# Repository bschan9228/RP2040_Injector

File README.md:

The RP2040 Injector is a 4-layer PCB. It is essentially used as a keystroke injector. I sourced components, made the schematics and designed the PCB, and hand soldered the components onto a two-sided PCB. It utilizes an RP2040, voltage regulator, a USB Type-A connector.

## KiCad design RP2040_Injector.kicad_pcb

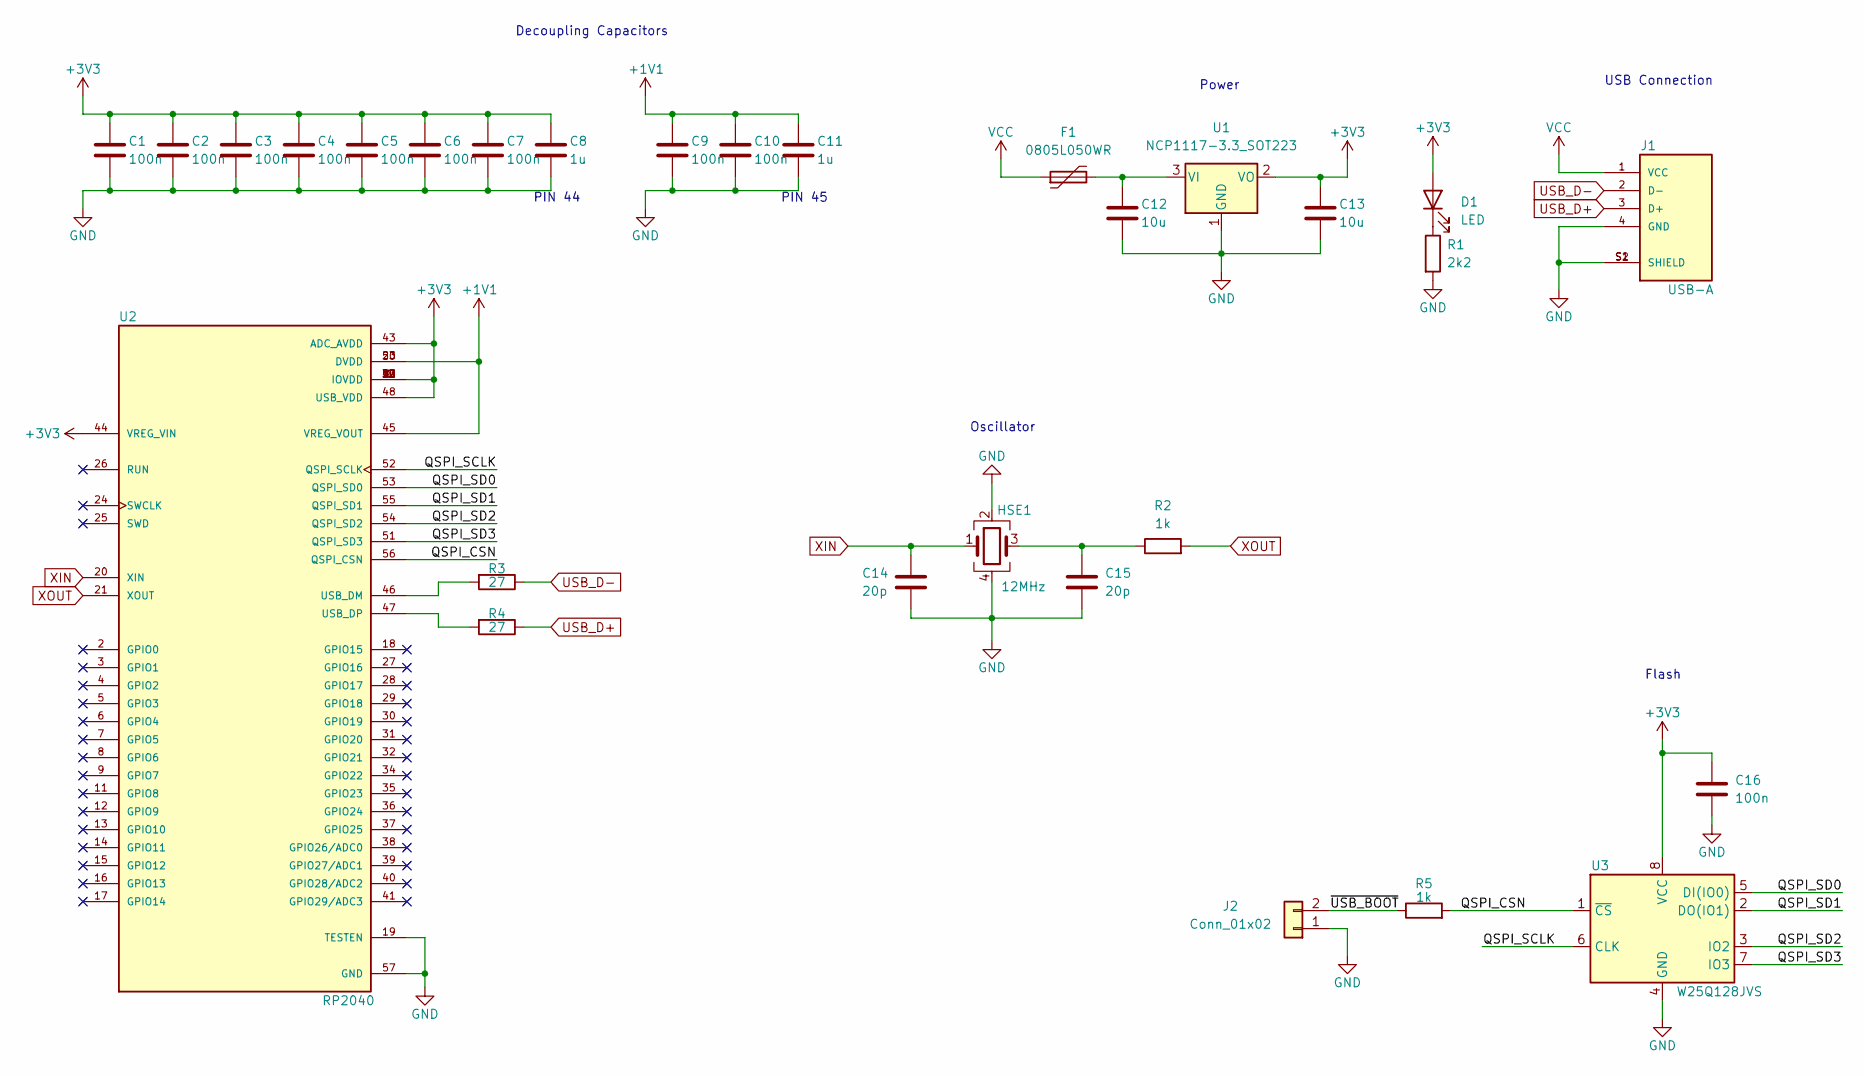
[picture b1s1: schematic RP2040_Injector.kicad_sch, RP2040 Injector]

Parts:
C1, C2, C3, C4, C5, C6, C7, C9, C10, C16: 100n; C_0402_1005Metric
C8, C11: 1u; C_0402_1005Metric
C12, C13: 10u; C_0805_2012Metric
C14, C15: 20p; C_0402_1005Metric
D1: LED; LED_0603_1608Metric
F1: 0805L050WR; Fuse_0805_2012Metric
HSE1: 12MHz; Crystal_SMD_SeikoEpson_FA238-4Pin_3.2x2.5mm
J1: USB-A; MOLEX_48037-0001; PARTREV D
J2: Conn_01x02; PinHeader_1x02_P2.00mm_Vertical
R1: 2k2; R_0402_1005Metric
R2, R5: 1k; R_0402_1005Metric
R3, R4: 27; R_0402_1005Metric
U1: NCP1117-3.3_SOT223; SOT-223-3_TabPin2
U2: RP2040; QFN40P700X700X90-57N; PARTREV 1.6.1
U3: W25Q128JVS; SOIC-8_5.23x5.23mm_P1.27mm

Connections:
+1V1: C9.1, C10.1, C11.1, U2.23 (DVDD), U2.45 (VREG_VOUT), U2.50 (DVDD)
+3V3: C1.1, C2.1, C3.1, C4.1, C5.1, C6.1, C7.1, C8.1, C13.1, C16.1, D1.2 (A), U1.2 (VO), U2.1 (IOVDD), U2.10 (IOVDD), U2.22 (IOVDD), U2.33 (IOVDD), U2.42 (IOVDD), U2.43 (ADC_AVDD), U2.44 (VREG_VIN), U2.48 (USB_VDD), U2.49 (IOVDD), U3.8 (VCC)
/QSPI_CSN: R5.2, U2.56 (QSPI_CSN), U3.1 (~CS)
/QSPI_SCLK: U2.52 (QSPI_SCLK), U3.6 (CLK)
/QSPI_SD0: U2.53 (QSPI_SD0), U3.5 (DI(IO0))
/QSPI_SD1: U2.55 (QSPI_SD1), U3.2 (DO(IO1))
/QSPI_SD2: U2.54 (QSPI_SD2), U3.3 (IO2)
/QSPI_SD3: U2.51 (QSPI_SD3), U3.7 (IO3)
/~USB_BOOT: J2.2, R5.1
GND: C1.2, C2.2, C3.2, C4.2, C5.2, C6.2, C7.2, C8.2, C9.2, C10.2, C11.2, C12.2, C13.2, C14.2, C15.2, C16.2, HSE1.2, HSE1.4, J1.4 (GND), J1.S1 (SHIELD), J1.S2 (SHIELD), J2.1, R1.2, U1.1 (GND), U2.19 (TESTEN), U2.57 (GND), U3.4 (GND)
unnamed: C12.1, F1.2, U1.3 (VI)
unnamed: C15.1, HSE1.3, R2.1
unnamed: D1.1 (K), R1.1
unnamed: R3.2, U2.46 (USB_DM)
unnamed: R4.2, U2.47 (USB_DP)
USB_D+: J1.3 (D+), R4.1
USB_D-: J1.2 (D-), R3.1
VCC: F1.1, J1.1 (VCC)
XIN: C14.1, HSE1.1, U2.20 (XIN)
XOUT: R2.2, U2.21 (XOUT)

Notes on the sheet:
PIN 45
Oscillator
PIN 44
Decoupling Capacitors
Flash
Power
USB Connection

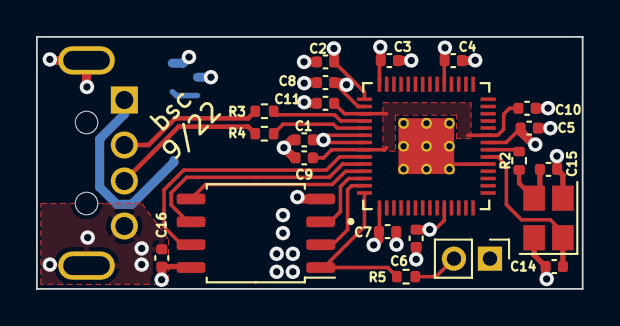
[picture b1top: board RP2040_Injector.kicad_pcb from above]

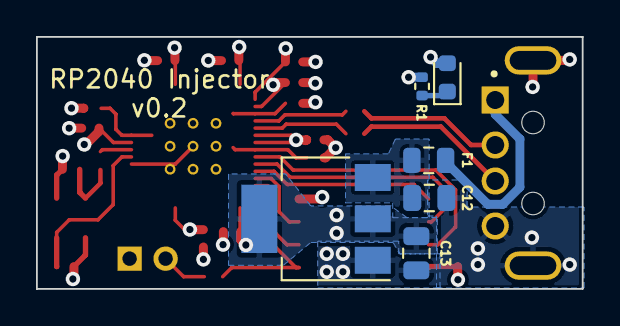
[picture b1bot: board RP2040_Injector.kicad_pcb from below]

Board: 4 copper layers, 30.3 x 14.0 mm, 29 parts (7 on the bottom side), 20 nets.

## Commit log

2022-08-26 Finished v0.1 PCB wiring
2022-08-26 Finished PCB wiring
2022-08-26 Finalized v0.1 design
2022-08-28 Started v0.2
2022-08-28 Finished wiring
2022-08-29 Completed v0.2
